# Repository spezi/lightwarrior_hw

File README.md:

# lightwarrior_hw
All lightwarrior hardware related stuff

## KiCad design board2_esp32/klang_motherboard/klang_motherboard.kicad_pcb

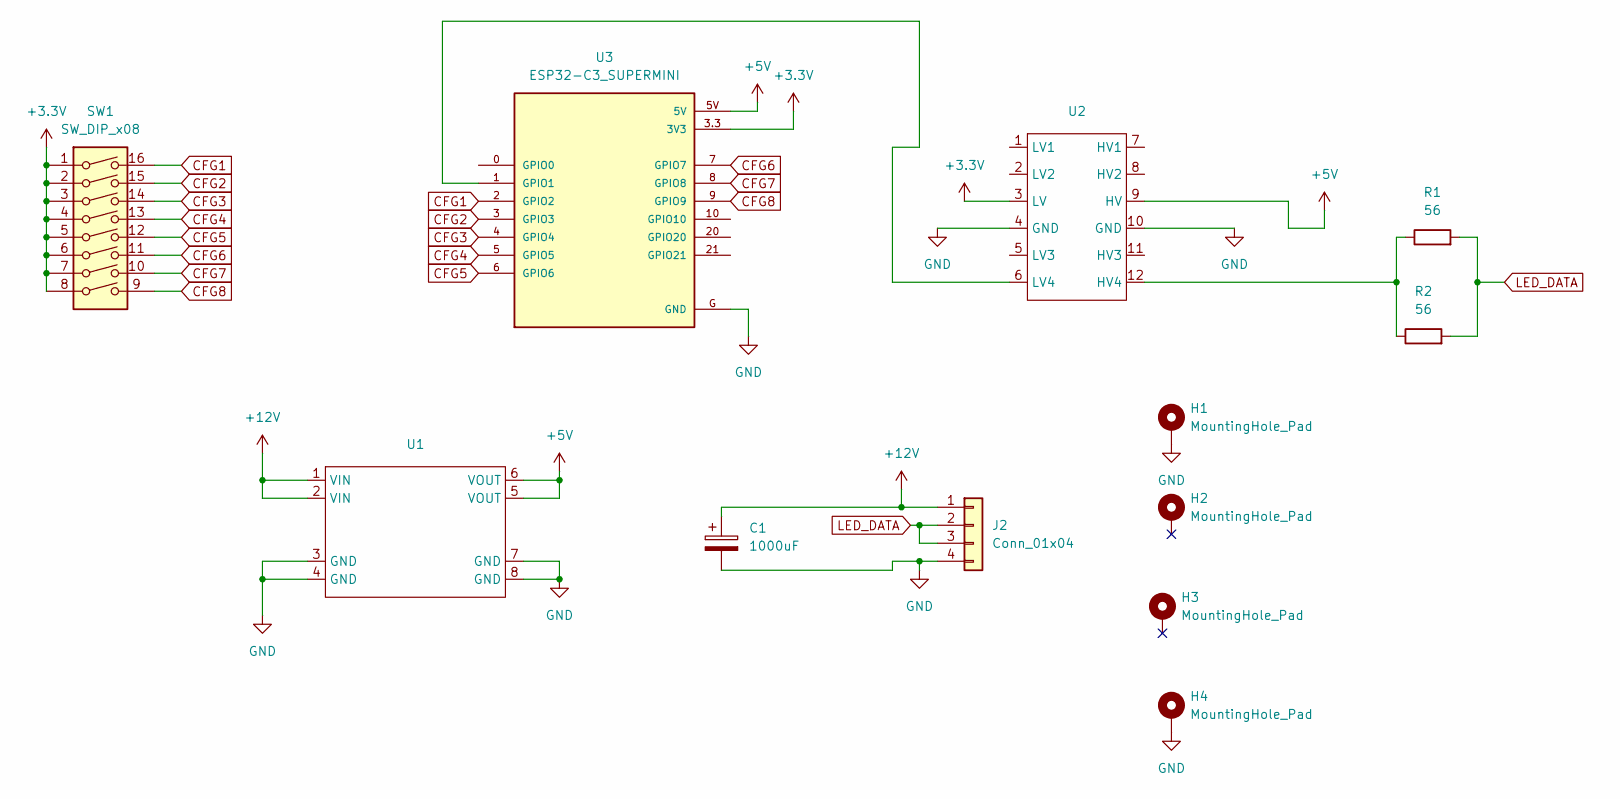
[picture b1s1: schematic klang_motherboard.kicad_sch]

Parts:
C1: 1000uF; CP_Radial_D10.0mm_P5.00mm
H1, H2, H3, H4: MountingHole_Pad; MountingHole_3.2mm_M3_DIN965_Pad_TopBottom
J2: Conn_01x04; SolderWire-0.75sqmm_1x04_P7mm_D1.25mm_OD3.5mm_Relief
R1: 56; R_0805_2012Metric
R2: 56; R_Axial_DIN0207_L6.3mm_D2.5mm_P7.62mm_Horizontal
SW1: SW_DIP_x08; SW_DIP_SPSTx08_Slide_6.7x21.88mm_W7.62mm_P2.54mm_LowProfile
U1: MINI560_tht_smd_combo
U2: LOGIC LEVEL CONVERTER 4 FOOTPRINT
U3: ESP32-C3_SUPERMINI; MODULE_ESP32-C3_SUPERMINI

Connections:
+3.3V: SW1.1, SW1.2, SW1.3, SW1.4, SW1.5, SW1.6, SW1.7, SW1.8, U2.3 (LV), U3.3.3 (3V3)
+5V: U1.5 (VOUT), U1.6 (VOUT), U2.9 (HV), U3.5V
+12V: C1.1, J2.1, U1.1 (VIN), U1.2 (VIN)
CFG1: SW1.16, U3.2 (GPIO2)
CFG2: SW1.15, U3.3 (GPIO3)
CFG3: SW1.14, U3.4 (GPIO4)
CFG4: SW1.13, U3.5 (GPIO5)
CFG5: SW1.12, U3.6 (GPIO6)
CFG6: SW1.11, U3.7 (GPIO7)
CFG7: SW1.10, U3.8 (GPIO8)
CFG8: SW1.9, U3.9 (GPIO9)
GND: C1.2, H1.1, H4.1, J2.4, U1.3 (GND), U1.4 (GND), U1.7 (GND), U1.8 (GND), U2.4 (GND), U2.10 (GND), U3.G (GND)
LED_DATA: J2.2, J2.3, R1.2, R2.2
unnamed: R1.1, R2.1, U2.12 (HV4)
unnamed: U2.6 (LV4), U3.1 (GPIO1)

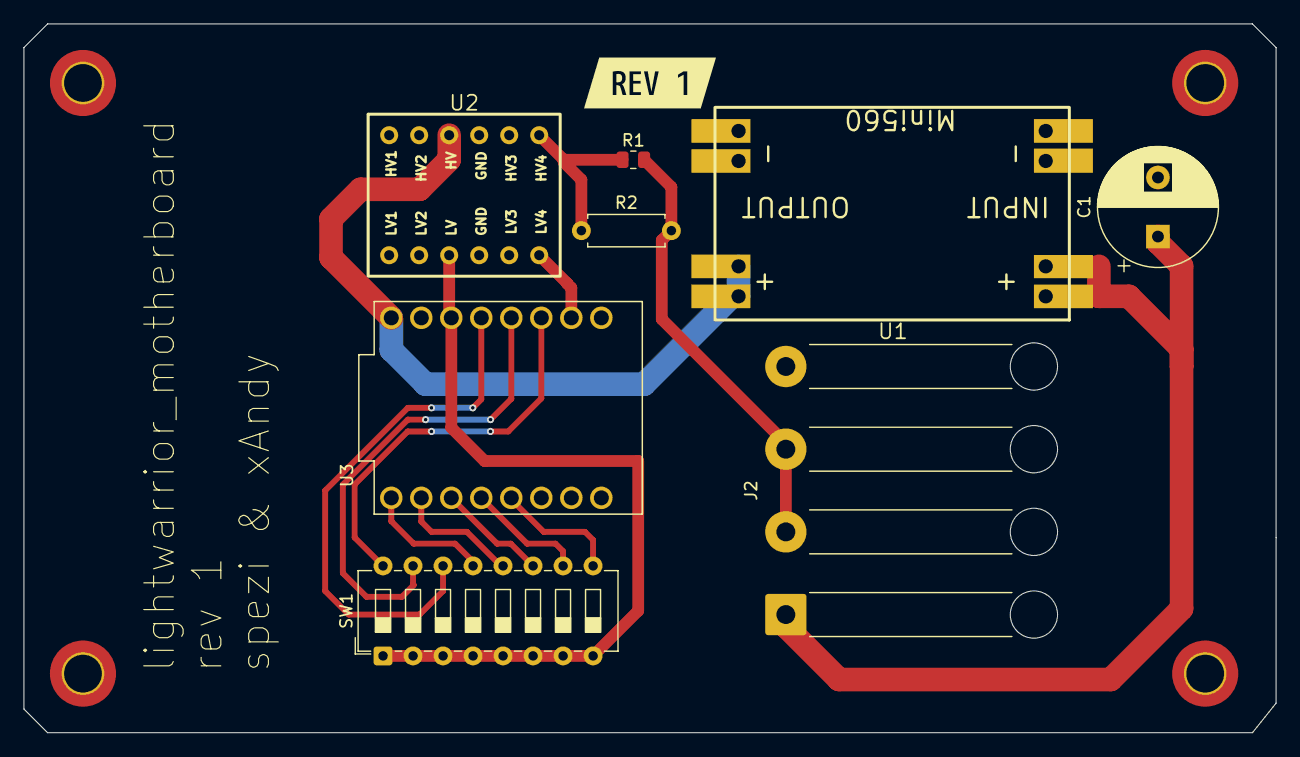
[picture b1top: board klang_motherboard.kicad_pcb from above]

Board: 2 copper layers, 106.0 x 60.0 mm, 14 parts (1 on the bottom side), 15 nets.

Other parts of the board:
kibuzzard-686AEEB4, kibuzzard-686AEEB4#2: G***; kibuzzard-686AEEB4

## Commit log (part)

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2025-07-08 get recent files
2025-07-08 mv files
2025-07-10 3D Netzteilcase hinzugefügt
2025-07-19 add first pcb board version
2025-07-20 start esp32c3 port
2025-07-20 initial DIP support, remove artnet
2025-07-20 add cases
2025-07-21 simplify platformio config
2025-07-21 first multi frame tpm2 poc
2025-07-21 working tpm2 fragmentation
2025-07-21 add case parts
2025-07-22 fix frame offset calculation, add debug stats
2025-07-23 add wip multi output tpm2
2025-07-23 add loop and wifi stats
